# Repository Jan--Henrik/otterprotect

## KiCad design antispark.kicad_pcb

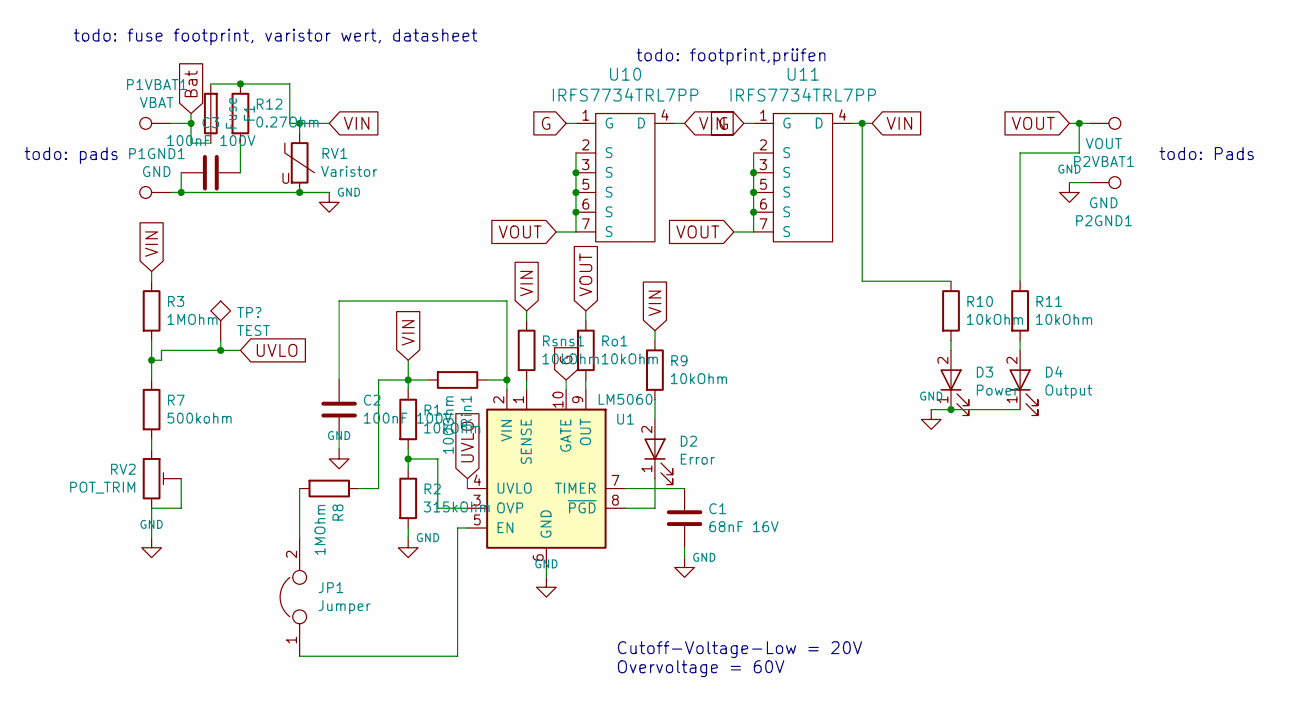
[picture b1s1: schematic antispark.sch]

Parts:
C1: 68nF 16V; C_0603
C2, C3: 100nF 100V; C_0805
D2: Error; LED_0603
D3: Power; LED_0603
D4: Output; LED_0603
F1: Fuse; CarfuseMaxi
JP1: Jumper; smdJumper1x2
P1GND1, P2GND1: GND; 1PAD_6x5mm
P1VBAT1: VBAT; 1PAD_6x5mm
P2VBAT1: VOUT; 1PAD_6x5mm
R1, R9, R10, R11: 10kOhm; R_1206
R2: 315kOhm; R_0603
R3: 1MOhm; R_1206
R7: 500kohm; R_0603
R8: 1MOhm; R_0603
R12: 0.27Ohm; R_1206
RV1: Varistor; RV_Disc_D21.5_W6.3_P10
RV2: POT_TRIM; Potentiometer_Trimmer_Bourns_3266P
Rin1: 100Ohm; R_1206
Ro1: 10kOhm; R_0603
Rsns1: 10kOhm; R_0603
U1: LM5060; MSOP-10_3x3mm_Pitch0.5mm
U10, U11: IRFS7734TRL7PP; D2PAK-7-GDS

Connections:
Bat: F1.1, P1VBAT1.1
G: U1.10 (GATE), U10.1 (G), U11.1 (G)
GND: C1.2, C2.2, C3.2, D3.1 (K), D4.1 (K), P1GND1.1, P2GND1.1, R2.2, RV1.2, RV2.2, RV2.3, U1.6 (GND)
unnamed: C1.1, U1.7 (TIMER)
unnamed: C2.1, Rin1.1, U1.2 (VIN)
unnamed: C3.1, R12.2
unnamed: D2.1 (K), U1.8 (~PGD)
unnamed: D2.2 (A), R9.2
unnamed: D3.2 (A), R10.2
unnamed: D4.2 (A), R11.2
unnamed: JP1.1, U1.5 (EN)
unnamed: JP1.2, R8.2
unnamed: R1.2, R2.1, U1.3 (OVP)
unnamed: R7.2, RV2.1
unnamed: Ro1.2, U1.9 (OUT)
unnamed: Rsns1.2, U1.1 (SENSE)
UVLO: R3.2, R7.1, U1.4 (UVLO)
VIN: F1.2, R1.1, R3.1, R8.1, R9.1, R10.1, R12.1, RV1.1, Rin1.2, Rsns1.1, U10.4 (D), U11.4 (D)
VOUT: P2VBAT1.1, R11.1, Ro1.1, U10.2 (S), U10.3 (S), U10.5 (S), U10.6 (S), U10.7 (S), U11.2 (S), U11.3 (S), U11.5 (S), U11.6 (S), U11.7 (S)

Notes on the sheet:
todo: Pads
todo: footprint,prüfen
todo: fuse footprint, varistor wert, datasheet
todo: pads
Cutoff-Voltage-Low = 20V Overvoltage = 60V

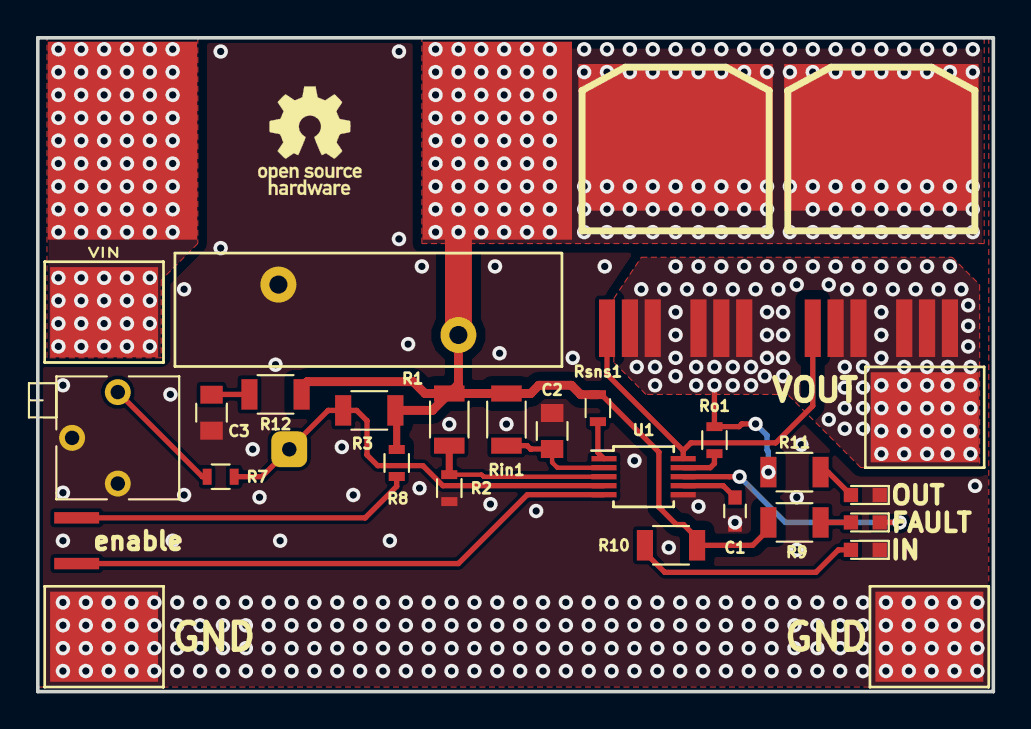
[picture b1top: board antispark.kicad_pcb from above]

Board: 2 copper layers, 53.1 x 36.3 mm, 29 parts (0 on the bottom side), 19 nets.

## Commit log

2019-02-26 added gitignore
2019-02-26 added files
2019-02-26 removed files
